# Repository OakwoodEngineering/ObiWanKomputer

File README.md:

# Obi Wan Komputer and Combined Payload Board
## Oakwood Engineering, NyanSat Project

Welcome to the public git repository for NyanSat's OBC and payload board.  We hope that this project will be generally useful for the CubeSat community.  NyanSat is a 2U CubeSat selected by NASA's CubeSat Launch Initiative and made by high school students at [Oakwood School](https://oakwoodway.org).

[NyanSat Obi Wan Komputer and Combined Payload Board](https://github.com/OakwoodEngineering/ObiWanKomputer) by [Oakwood Engineering](https://nyansat.org) is licensed under [Creative Commons Attribution-ShareAlike 4.0 International](https://creativecommons.org/licenses/by-sa/4.0/?ref=chooser-v1)    

It is based on the [PyCubed](https://pycubed.org) flight computer by Max Holliday.

The design was made with [Kicad EDA](https://www.kicad.org/) version 8 and is in the hardware directory.  More details to come.

For now, an overview of the design is in the following poster presented at Cal Poly's [CubeSat Developer Workshop](https://www.cubesatdw.org/) 2025 (click for PDF):

You can also visit our website at [nyansat.org](https://nyansat.org).

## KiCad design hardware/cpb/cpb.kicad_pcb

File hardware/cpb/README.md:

# NyanSat
## Combined Payload Board

The Combined Payload Board (CPB) is a component of the NyanSat project, designed to interface with a variety of payloads, including imaging, material science experiments, the Attitude Determination and Control Subsystem (ADACS), and the acoustic spacecraft mapping subsystem.

### Internal Interfaces
* Mechanical: PC/104 form factor for holes and board outline.
    * SMT components all on bottom side of board; top side for connectors and stacking Raspberry Pi Zero 2W.
* 40 pin spacecraft electrical bus
	* Battery voltage (post-inhibit switches, current sensing, current limiting on OBC).
	* One GPIO: Gating of battery voltage to board except bridge driver
    * One GPIO: Gating of battery voltage to bridge driver
	* I2C
		* I2C-UART Address: `0x90 = 1001 0000`
            * Raspberry Pi: controlled by serial from I2C-UART.
            * Pi power controlled by I2C-UART GPIO
            * 3 external power switches controlled by I2C-UART GPIOs.
        * I2C-SPI converter for driver bridges `0x50 = 0101 000X`
            * MAX22200 bridge chip select, command select, and enable controlled by I2C-SPI converter.
		* Microcontroller Address: TBD
	* Ground/return path for power and all signals
* Mounting holes
	* 0603 pads from holes to board ground exist; can populate with capacitor (AC-couple to stack), resistor, short, or leave open.

### External Interfaces
* 4 versatile analog inputs. provided by microcontroller ADC, 0-3.3V 12 bit 1.1MSPS.  Pads on board allow selections of various modes:
	* Divided voltage or pulled towards chosen voltage
	* Resistive termination or known impedance
	* AC coupling
    * Pin alternate functions allow use for digital inputs or timer outputs
* 2 DC (0-5V) or AC-coupled waveform generation channels produced from microcontroller DAC with ~40mA drive capability
	* Controlled by microcontroller; feedback to ADC allows precise control of voltages.
	* Low pass filter: 2nd order with -3dB bandwidth of 100KHz.
* 8 high-side switches of battery voltage for payloads and magnetorquers
	* 3 controlled by GPIO from I2C-UART peripheral
	* 1 controlled by onboard Raspberry Pi computer
	* 4 controlled by onboard Cortex-M0+ microcontroller
* 8 half-bridges with programmable current limits
* 5 pin connection for external I2C peripheral (e.g. magnetometer)
* On Pi: CSI interface for Raspberry Pi camera

### Anticipated Use
* Attitude Determination and Control Subsystem (ADACS):
	* Switches: 3 magnetorquers, bipolar (6 half-bridges)
* Acoustic Spacecraft Sounding:
	* Switch: Solenoid, driven by pair of half-bridges
	* Possible switch: MEMS microphone power
	* ADC: 2 channels of MEMS microphone.
* Material science / semiconductor characterization experiment  
	* Waveform generation: 2 channels of drive voltages.
	* ADC: 2 channels of measurement.
* Camera
	* Pi/CSI to camera.
	* Possible high powered LED via high side driver.
* Deployables
	* Option open to use high-side switches channels from here for deployment.
	* Consider using this board to energize second deployable resistor for redundancy.

### Stored-Program Computing Components
* Microcontroller; used mostly as a smart ADC/DAC.
	* STM32L072RBT6; 32MHz Cortex-M0+ with single-cycle multiplier, 128k flash, 6k data EEPROM, 20k RAM.
* Raspberry Pi Zero 2W; used mostly as interface for camera.
	* Quad-core Cortex A53 64-bit processor, 512MB SDRAM.
	* Wireless capabilities (disabled in flight) can be used for ground troubleshooting.
	* Use SLC microSD card, e.g. SFSD2048N1BN1WI-E-QF-111-STD from SwissBit.

### Design Philosophy
* Board's power is gated and will be completely de-powered if a pin on spacecraft electrical bus is not driven high.
* Seperate power gate for magnetorquer full-bridge.
* No high-level sequencing of experiments performed by this board; enabled and commanded from main On-Board Computer (OBC).
* I2C is isolated from spacecraft bus if de-powered or peripheral locks up.
* Large portions of functionality work even if non-volatile memory on a device is corrupted.
	* I2C-UART/GPIO chip does not have nonvolatile memory, and directly controls 4 output switches.
    * I2C-SPI and MAX22200 do not have nonvolatile state.
	* Microcontroller starts up held in reset until explicitly enabled by I2C-UART.
	* If microcontroller is corrupted, Raspberry Pi is capable of reprogramming via on-chip debug features.
    * Pi's power supply is separately enabled by I2C-UART.
	* If Pi filesystem is corrupted, small chance of recovery through failsafe pin (indicates to boot from different part of SD card).

### Known Weaknesses & Shortcomings
* No provision to measure power used by this board.
* No real current limiting beyond master current limiting from ADM1176 PMIC on OBC.
	* But: If entire satellite resets due to overcurrent, this board will revert to default state (turned off).
    * 200 mohm resistors and FET Rds do provide a little bit of mitigation of catastrophes.
* Raspberry Pi must be turned on to generate waveforms / run matsci experiment due to board architecture (needs 5V rail).
* Only having 4 ADC is a little limiting.

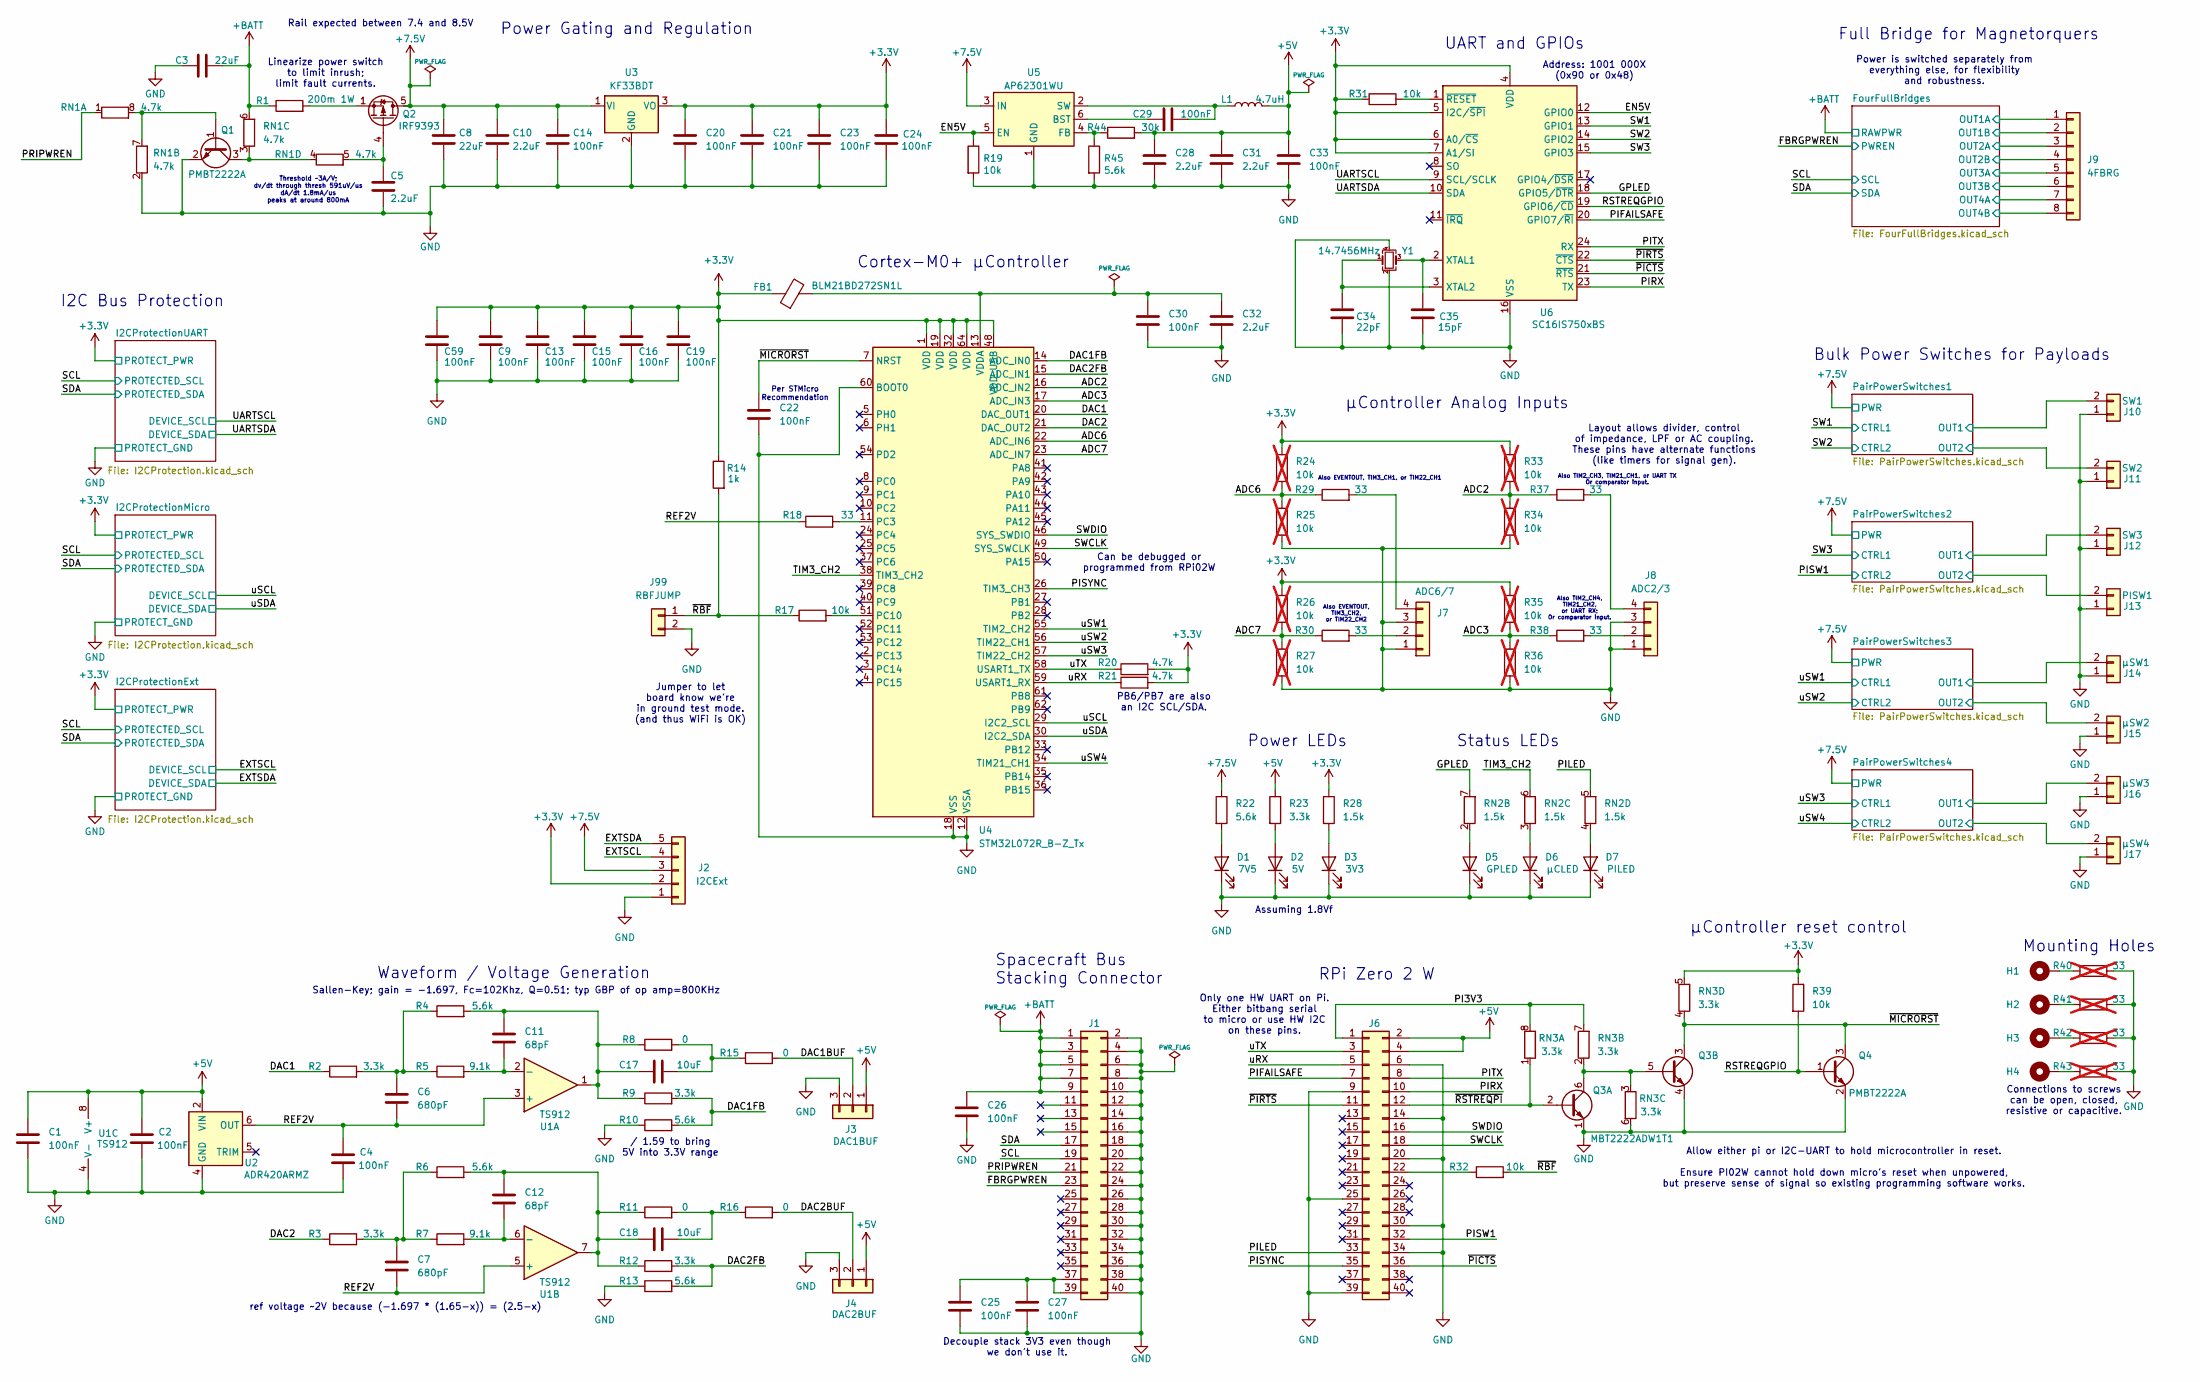
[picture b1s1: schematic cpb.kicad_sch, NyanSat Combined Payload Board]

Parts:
C1, C2, C4, C9, C13, C14, C15, C16, C19, C20, C21, C22, C23, C24, C25, C26, C27, C29, C30, C33, C59: 100nF; C_0603_1608Metric
C3, C8: 22uF; C_0805_2012Metric
C5, C10, C28, C31, C32: 2.2uF; C_0603_1608Metric
C6, C7: 680pF; C_0603_1608Metric
C11, C12: 68pF; C_0603_1608Metric
C17, C18: 10uF; C_0603_1608Metric
C34: 22pF; C_0603_1608Metric
C35: 15pF; C_0603_1608Metric
D1: 7V5; LED_0805_2012Metric; LCSC C84256
D2: 5V; LED_0805_2012Metric; LCSC C84256
D3: 3V3; LED_0805_2012Metric; LCSC C84256
D5: GPLED; LED_0805_2012Metric; LCSC C84256
D6: μCLED; LED_0805_2012Metric; LCSC C84256
D7: PILED; LED_0805_2012Metric; LCSC C84256
FB1: BLM21BD272SN1L; L_0805_2012Metric; LCSC C85839
H1, H2, H3, H4: MountingHole_Pad; MountingHole_3.2mm_M3_DIN965_Pad
J1: Spacecraft Bus Stacking Connector; PinHeader_2x20_P2.54mm_Vertical
J2: I2CExt; JST_PH_B5B-PH-K_1x05_P2.00mm_Vertical
J3: DAC1BUF; JST_PH_B3B-PH-K_1x03_P2.00mm_Vertical
J4: DAC2BUF; JST_PH_B3B-PH-K_1x03_P2.00mm_Vertical
J6: Raspberry Pi Zero 2W; RPI02W
J7: ADC6/7; JST_PH_B4B-PH-K_1x04_P2.00mm_Vertical
J8: ADC2/3; JST_PH_B4B-PH-K_1x04_P2.00mm_Vertical
J9: 4FBRG; JST_PHD_B8B-PHDSS_2x04_P2.00mm_Vertical
J10: SW1; JST_PH_B2B-PH-K_1x02_P2.00mm_Vertical
J11: SW2; JST_PH_B2B-PH-K_1x02_P2.00mm_Vertical
J12: SW3; JST_PH_B2B-PH-K_1x02_P2.00mm_Vertical
J13: PISW1; JST_PH_B2B-PH-K_1x02_P2.00mm_Vertical
J14: μSW1; JST_PH_B2B-PH-K_1x02_P2.00mm_Vertical
J15: μSW2; JST_PH_B2B-PH-K_1x02_P2.00mm_Vertical
J16: μSW3; JST_PH_B2B-PH-K_1x02_P2.00mm_Vertical
J17: μSW4; JST_PH_B2B-PH-K_1x02_P2.00mm_Vertical
J99: RBFJUMP; SolderJumper-2_P1.3mm_Open_TrianglePad1.0x1.5mm
L1: 4.7uH; L_Vishay_IHLP-2020; LCSC C844991
Q1, Q4: PMBT2222A; SOT-23; LCSC C23869
Q2: IRF9393; SOIC-8_3.9x4.9mm_P1.27mm; LCSC C520642
Q3: MBT2222ADW1T1; SOT-363_SC-70-6; LCSC C157366
R1: 200m 1W; R_1206_3216Metric
R2, R3, R9, R12, R23: 3.3k; R_0603_1608Metric
R4, R6, R10, R13, R22, R45: 5.6k; R_0603_1608Metric
R5, R7: 9.1k; R_0603_1608Metric
R8, R11, R15, R16: 0; R_0603_1608Metric
R14: 1k; R_0603_1608Metric
R17, R19, R31, R32, R39: 10k; R_0603_1608Metric
R18, R29, R30, R37, R38: 33; R_0603_1608Metric
R20, R21: 4.7k; R_0603_1608Metric
R24, R25, R26, R27, R33, R34, R35, R36: 10k; R_0603_1608Metric; not fitted
R28: 1.5k; R_0603_1608Metric
R40, R41, R42, R43: 33; R_0603_1608Metric; not fitted
R44: 30k; R_0603_1608Metric
RN1: 4.7k; R_Array_Convex_4x0603
RN2: 1.5k; R_Array_Convex_4x0603
RN3: 3.3k; R_Array_Convex_4x0603
U1: TS912; SOIC-8_3.9x4.9mm_P1.27mm; LCSC C73655
U2: ADR420ARMZ; MSOP-8_3x3mm_P0.65mm; LCSC C208143
U3: KF33BDT; TO-252-2; LCSC C283274
U4: STM32L072R_B-Z_Tx; LQFP-64_10x10mm_P0.5mm; LCSC C915968
U5: AP62301WU; TSOT-23-6
U6: SC16IS750xBS; HVQFN-24-1EP_4x4mm_P0.5mm_EP2.5x2.5mm; LCSC C2651891
Y1: 14.7456MHz; Crystal_SMD_3225-4Pin_3.2x2.5mm

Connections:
+3.3V: C9.1, C13.1, C15.1, C16.1, C19.1, C20.1, C21.1, C23.1, C24.1, C59.1, FB1.1, J2.2, R14.1, R20.2, R21.2, R24.1, R26.1, R28.1, R31.1, R33.1, R35.1, R39.1, RN3.5 (R4.2), U3.3 (VO), U4.1 (VDD), U4.19 (VDD), U4.32 (VDD), U4.48 (VDD_USB), U4.64 (VDD), U6.4 (VDD), U6.5 (I2C/~SPI), U6.6 (A0/~CS), U6.7 (A1/SI); also elsewhere on the board
+5V: C1.1, C2.1, C28.1, C31.1, C33.1, J3.1, J4.1, J6.2, J6.4, L1.2, R23.1, R44.2, U1.8 (V+), U2.2 (VIN)
+7.5V: C8.1, C10.1, C14.1, J2.3, Q2.5 (D), Q2.6 (D), Q2.7 (D), Q2.8 (D), R22.1, U3.1 (VI), U5.3 (IN); also elsewhere on the board
+BATT: C3.2, C26.1, J1.1, J1.3, J1.5, J1.7, J1.9, R1.1, RN1.6 (R3.2); also elsewhere on the board
/ADC2: R33.2, R34.1, R37.1, U4.16 (ADC_IN2)
/ADC3: R35.2, R36.1, R38.1, U4.17 (ADC_IN3)
/ADC6: R24.2, R25.1, R29.1, U4.22 (ADC_IN6)
/ADC7: R26.2, R27.1, R30.1, U4.23 (ADC_IN7)
/DAC1: R2.1, U4.20 (DAC_OUT1)
/DAC1BUF: J3.2, R15.2
/DAC1FB: R9.2, R10.2, U4.14 (ADC_IN0)
/DAC2: R3.1, U4.21 (DAC_OUT2)
/DAC2BUF: J4.2, R16.2
/DAC2FB: R12.2, R13.2, U4.15 (ADC_IN1)
/EN5V: R19.1, U5.5 (EN), U6.12 (GPIO0)
/EXTSCL: J2.4; also elsewhere on the board
/EXTSDA: J2.5; also elsewhere on the board
/FBRGPWREN: J1.23; also elsewhere on the board
/FourFullBridges/OUT1A: J9.1; also elsewhere on the board
/FourFullBridges/OUT1B: J9.2; also elsewhere on the board
/FourFullBridges/OUT2A: J9.3; also elsewhere on the board
/FourFullBridges/OUT2B: J9.4; also elsewhere on the board
/FourFullBridges/OUT3A: J9.5; also elsewhere on the board
/FourFullBridges/OUT3B: J9.6; also elsewhere on the board
/FourFullBridges/OUT4A: J9.7; also elsewhere on the board
/FourFullBridges/OUT4B: J9.8; also elsewhere on the board
/GPLED: RN2.7 (R2.2), U6.18 (GPIO5/~DTR)
/PI3V3: J6.1, RN3.7 (R2.2), RN3.8 (R1.2)
/PIFAILSAFE: J6.7, U6.20 (GPIO7/~RI)
/PILED: J6.33, RN2.5 (R4.2)
/PIRX: J6.10, U6.23 (TX)
/PISW1: J6.32; also elsewhere on the board
/PISYNC: J6.35, U4.26 (TIM3_CH3)
/PITX: J6.8, U6.24 (RX)
/PRIPWREN: J1.21, RN1.1 (R1.1)
/PairPowerSwitches1/OUT1: J10.2; also elsewhere on the board
/PairPowerSwitches1/OUT2: J11.2; also elsewhere on the board
/PairPowerSwitches2/OUT1: J12.2; also elsewhere on the board
/PairPowerSwitches2/OUT2: J13.2; also elsewhere on the board
/PairPowerSwitches3/OUT1: J14.2; also elsewhere on the board
/PairPowerSwitches3/OUT2: J15.2; also elsewhere on the board
/PairPowerSwitches4/OUT1: J16.2; also elsewhere on the board
/PairPowerSwitches4/OUT2: J17.2; also elsewhere on the board
/REF2V: C4.1, C6.2, C7.2, R18.1, U1.3 (+), U1.5 (+), U2.6 (OUT)
/RSTREQGPIO: Q4.1 (B), R39.2, U6.19 (GPIO6/~CD)
/SCL: J1.19; also elsewhere on the board
/SDA: J1.17; also elsewhere on the board
/SW1: U6.13 (GPIO1); also elsewhere on the board
/SW2: U6.14 (GPIO2); also elsewhere on the board
/SW3: U6.15 (GPIO3); also elsewhere on the board
/SWCLK: J6.18, U4.49 (SYS_SWCLK)
/SWDIO: J6.16, U4.46 (SYS_SWDIO)
/TIM3_CH2: RN2.6 (R3.2), U4.38 (TIM3_CH2)
/UARTSCL: U6.9 (SCL/SCLK); also elsewhere on the board
/UARTSDA: U6.10 (SDA); also elsewhere on the board
/uRX: J6.5, R21.1, U4.59 (USART1_RX)
/uSCL: U4.29 (I2C2_SCL); also elsewhere on the board
/uSDA: U4.30 (I2C2_SDA); also elsewhere on the board
/uSW1: U4.55 (TIM2_CH2); also elsewhere on the board
/uSW2: U4.56 (TIM22_CH1); also elsewhere on the board
/uSW3: U4.57 (TIM22_CH2); also elsewhere on the board
/uSW4: U4.34 (TIM21_CH1); also elsewhere on the board
/uTX: J6.3, R20.1, U4.58 (USART1_TX)
/~MICRORST: C22.1, Q3.3 (C2), Q4.3 (C), RN3.4 (R4.1), U4.7 (NRST)
/~PICTS: J6.36, U6.21 (~RTS)
/~PIRTS: J6.11, U6.22 (~CTS)
/~RBF: J99.1, R14.2, R17.1, R32.2
/~RSTREQPI: J6.12, Q3.2 (B1), RN3.1 (R1.1)
GND: C1.2, C2.2, C3.1, C4.2, C5.2, C8.2, C9.2, C10.2, C13.2, C14.2, C15.2, C16.2, C19.2, C20.2, C21.2, C22.2, C23.2, C24.2, C25.2, C26.2, C27.2, C28.2, C30.2, C31.2, C32.2, C33.2, C34.2, C35.2, C59.2, D1.1 (K), D2.1 (K), D3.1 (K), D5.1 (K), D6.1 (K), D7.1 (K), J1.2, J1.4, J1.6, J1.8, J1.10, J1.12, J1.14, J1.16, J1.18, J1.20, J1.22, J1.24, J1.26, J1.28, J1.30, J1.32, J1.34, J1.36, J1.38, J1.40, J2.1, J3.3, J4.3, J6.6, J6.9, J6.14, J6.20, J6.25, J6.30, J6.34, J6.39, J7.1, J7.3, J8.1, J8.3, J10.1, J11.1, J12.1, J13.1, J14.1, J15.1, J16.1, J17.1, J99.2, Q1.2 (E), Q3.1 (E1), Q3.4 (E2), Q4.2 (E), R10.1, R13.1, R19.2, R25.2, R27.2, R34.2, R36.2, R40.2, R41.2, R42.2, R43.2, R45.2, RN1.2 (R2.1), RN3.6 (R3.2), U1.4 (V-), U2.4 (GND), U3.2 (GND), U4.12 (VSSA), U4.18 (VSS), U4.31 (VSS), U4.47 (VSS), U4.60 (BOOT0), U4.63 (VSS), U5.1 (GND), U6.16 (VSS), U6.25 (VSS), Y1.2, Y1.4; also elsewhere on the board
unnamed: C6.1, R2.2, R4.1, R5.1
unnamed: C7.1, R3.2, R6.1, R7.1
unnamed: C11.1, C17.1, R4.2, R8.1, R9.1, U1.1
unnamed: C12.1, C18.1, R6.2, R11.1, R12.1, U1.7
unnamed: C17.2, R8.2, R15.1
unnamed: C18.2, R11.2, R16.1
unnamed: D1.2 (A), R22.2
unnamed: D2.2 (A), R23.2
unnamed: D3.2 (A), R28.2
unnamed: D5.2 (A), RN2.2 (R2.1)
unnamed: D6.2 (A), RN2.3 (R3.1)
unnamed: D7.2 (A), RN2.4 (R4.1)
unnamed: H1.1, R40.1
unnamed: H2.1, R41.1
unnamed: H3.1, R42.1
unnamed: H4.1, R43.1
unnamed: C25.1, C27.1, J1.37, J1.39
unnamed: J6.22, R32.1
unnamed: J7.2, R30.2
unnamed: J7.4, R29.2
unnamed: J8.2, R38.2
unnamed: J8.4, R37.2
unnamed: Q1.1 (B), RN1.7 (R2.2), RN1.8 (R1.2)
unnamed: Q1.3 (C), RN1.3 (R3.1), RN1.4 (R4.1)
unnamed: C5.1, Q2.4 (G), RN1.5 (R4.2)
unnamed: Q2.1 (S), Q2.2 (S), Q2.3 (S), R1.2
unnamed: Q3.5 (B2), Q3.6 (C1), RN3.2 (R2.1), RN3.3 (R3.1)
unnamed: C11.2, R5.2, U1.2 (-)
unnamed: C12.2, R7.2, U1.6 (-)
unnamed: R18.2, U4.11 (PC3)
unnamed: R17.2, U4.51 (PC10)
unnamed: C30.1, C32.1, FB1.2, U4.13 (VDDA)
unnamed: C29.1, U5.6 (BST)
unnamed: R44.1, R45.1, U5.4 (FB)
unnamed: C29.2, L1.1, U5.2 (SW)
unnamed: C35.1, U6.2 (XTAL1), Y1.3
unnamed: C34.1, U6.3 (XTAL2), Y1.1
unnamed: R31.2, U6.1 (~RESET)

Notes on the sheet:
Also TIM2_CH3, TIM21_CH1, or UART TX Or comparator input.
Bulk Power Switches for Payloads
Connections to screws can be open, closed, resistive or capacitive.
μController Analog Inputs
Power LEDs
Can be debugged or programmed from RPi02W
Allow either pi or I2C-UART to hold microcontroller in reset. Ensure PI02W cannot hold down micro's reset when unpowered, but preserve sense of signal so existing programming software works.
Threshold ~3A/V; dv/dt through thresh 591uV/us dA/dt 1.8mA/us peaks at around 800mA
Only one HW UART on Pi. Either bitbang serial to micro or use HW I2C on these pins.
Decouple stack 3V3 even though we don't use it.
Power Gating and Regulation
ref voltage ~2V because (-1.697 * (1.65-x)) = (2.5-x)
PB6/PB7 are also an I2C SCL/SDA.
Also TIM2_CH4, TIM21_CH2, or UART RX; Or comparator input.
Rail expected between 7.4 and 8.5V
Power is switched separately from everything else, for flexibility and robustness.
Mounting Holes
μController reset control
Sallen-Key; gain = -1.697, Fc=102Khz, Q=0.51; typ GBP of op amp=800KHz
RPi Zero 2 W
Assuming 1.8Vf
Also EVENTOUT, TIM3_CH2, or TIM22_CH2
Layout allows divider, control of impedance, LPF or AC coupling. These pins have alternate functions (like timers for signal gen).
Address: 1001 000X (0x90 or 0x48)
Status LEDs
UART and GPIOs
Linearize power switch to limit inrush; limit fault currents.
Jumper to let board know we're in ground test mode. (and thus WiFi is OK)
Per STMicro Recommendation
/ 1.59 to bring 5V into 3.3V range
Spacecraft Bus Stacking Connector
Also EVENTOUT, TIM3_CH1, or TIM22_CH1
Waveform / Voltage Generation
Cortex-M0+ μController
Full Bridge for Magnetorquers
I2C Bus Protection

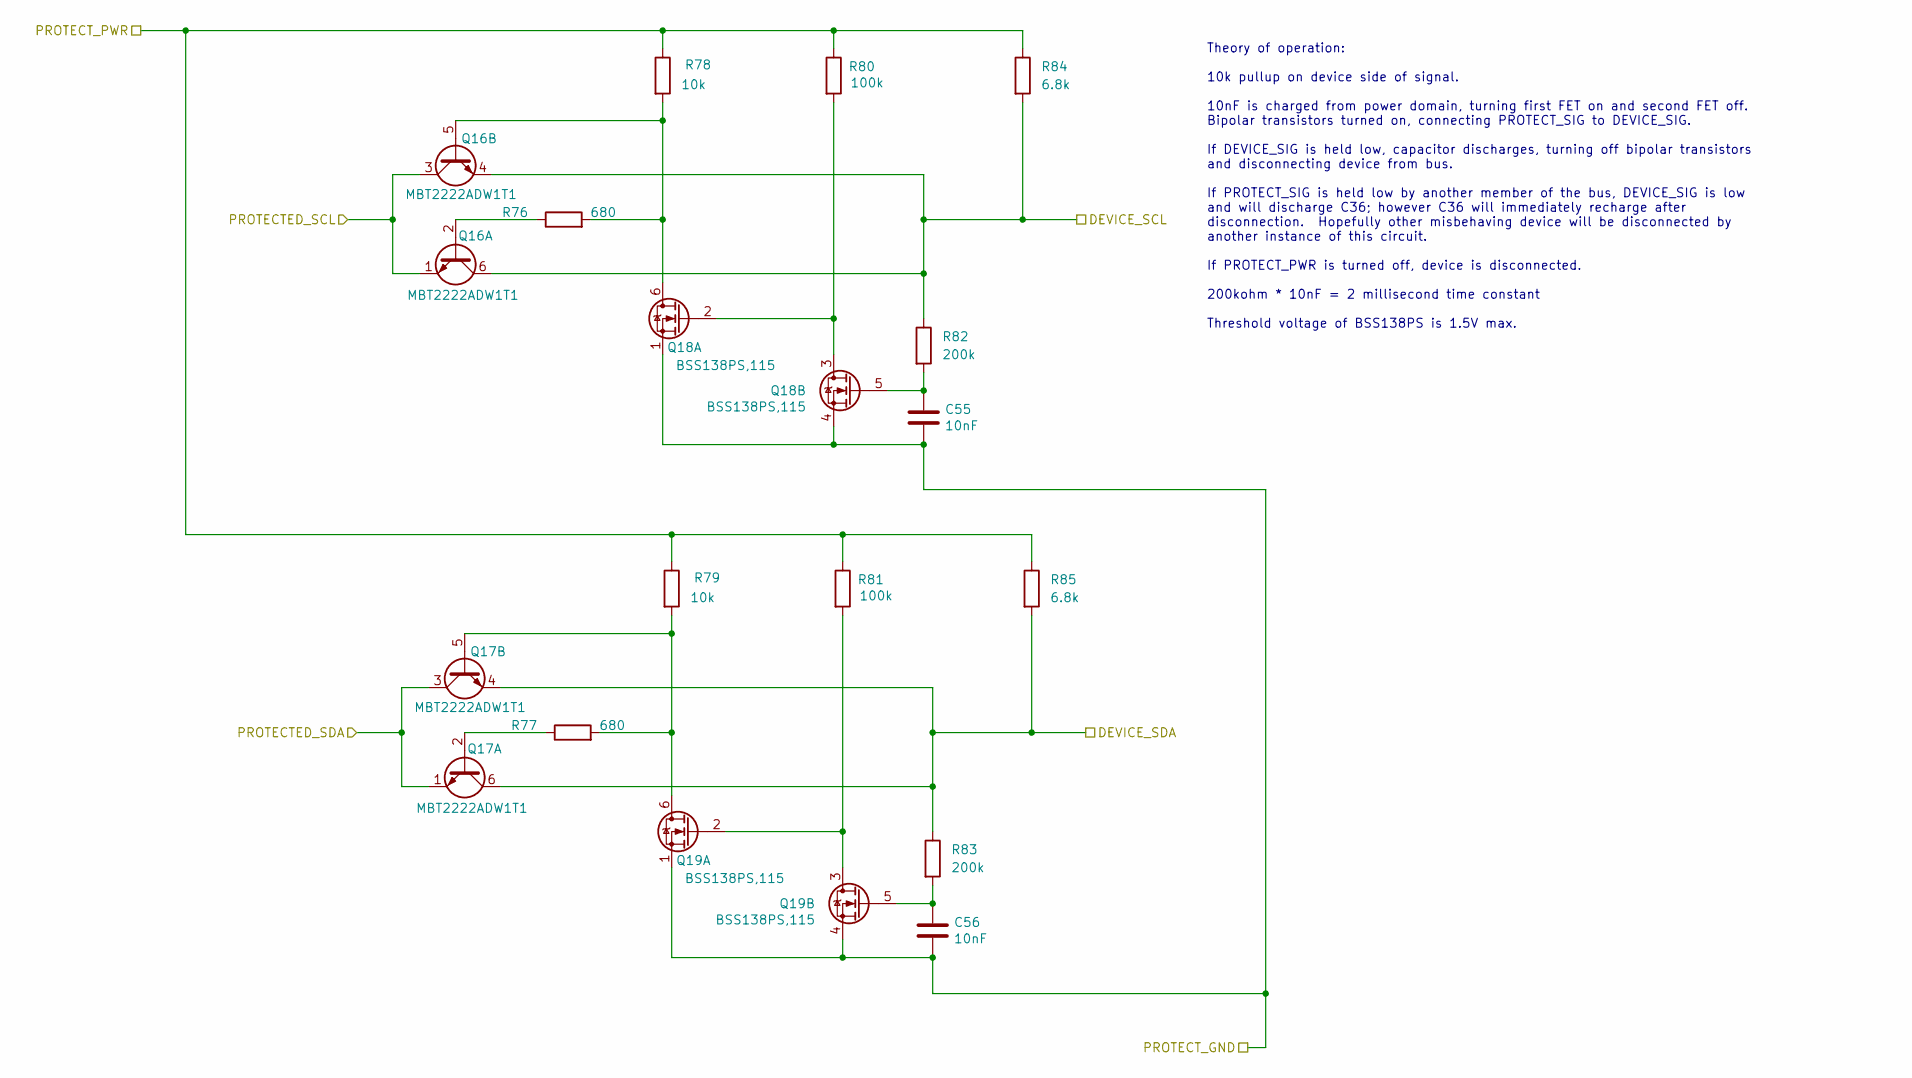
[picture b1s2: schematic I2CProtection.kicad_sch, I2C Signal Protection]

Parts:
C55, C56: 10nF; C_0603_1608Metric
Q16, Q17: MBT2222ADW1T1; SOT-363_SC-70-6; LCSC C157366
Q18, Q19: BSS138PS,115; SOT-363_SC-70-6; LCSC C193381
R76, R77: 680; R_0603_1608Metric
R78, R79: 10k; R_0603_1608Metric
R80, R81: 100k; R_0603_1608Metric
R82, R83: 200k; R_0603_1608Metric
R84, R85: 6.8k; R_0603_1608Metric

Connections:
+3.3V: R78.1, R79.1, R80.1, R81.1, R84.1, R85.1; also elsewhere on the board
/SCL: Q16.1 (E1), Q16.3 (C2); also elsewhere on the board
/SDA: Q17.1 (E1), Q17.3 (C2); also elsewhere on the board
/uSCL: Q16.4 (E2), Q16.6 (C1), R82.1, R84.2; also elsewhere on the board
/uSDA: Q17.4 (E2), Q17.6 (C1), R83.1, R85.2; also elsewhere on the board
GND: C55.2, C56.2, Q18.1 (S2), Q18.4 (S1), Q19.1 (S2), Q19.4 (S1); also elsewhere on the board
unnamed: Q16.2 (B1), R76.1
unnamed: Q16.5 (B2), Q18.6 (D1), R76.2, R78.2
unnamed: Q17.2 (B1), R77.1
unnamed: Q17.5 (B2), Q19.6 (D1), R77.2, R79.2
unnamed: Q18.2 (G2), Q18.3 (D2), R80.2
unnamed: C55.1, Q18.5 (G1), R82.2
unnamed: Q19.2 (G2), Q19.3 (D2), R81.2
unnamed: C56.1, Q19.5 (G1), R83.2

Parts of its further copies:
C51, C52, C53, C54, C57, C58: 10nF; C_0603_1608Metric
Q8, Q9, Q12, Q13, Q20, Q21: MBT2222ADW1T1; SOT-363_SC-70-6; LCSC C157366
Q10, Q11, Q14, Q15, Q22, Q23: BSS138PS,115; SOT-363_SC-70-6; LCSC C193381
R56, R57, R66, R67, R86, R87: 680; R_0603_1608Metric
R58, R59, R68, R69, R88, R89: 10k; R_0603_1608Metric
R60, R61, R70, R71, R90, R91: 100k; R_0603_1608Metric
R62, R63, R72, R73, R92, R93: 200k; R_0603_1608Metric
R64, R65, R74, R75, R94, R95: 6.8k; R_0603_1608Metric

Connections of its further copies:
+3.3V: R68.1, R69.1, R70.1, R71.1, R74.1, R75.1, R88.1, R89.1, R90.1, R91.1, R94.1, R95.1; also elsewhere on the board
/EXTSCL: Q20.4 (E2), Q20.6 (C1), R92.1, R94.2; also elsewhere on the board
/EXTSDA: Q21.4 (E2), Q21.6 (C1), R93.1, R95.2; also elsewhere on the board
/FourFullBridges/FBRDG3V3: R58.1, R59.1, R60.1, R61.1, R64.1, R65.1; also elsewhere on the board
/FourFullBridges/PCVTSCL: Q8.4 (E2), Q8.6 (C1), R62.1, R64.2; also elsewhere on the board
/FourFullBridges/PCVTSDA: Q9.4 (E2), Q9.6 (C1), R63.1, R65.2; also elsewhere on the board
/SCL: Q8.1 (E1), Q8.3 (C2), Q12.1 (E1), Q12.3 (C2), Q20.1 (E1), Q20.3 (C2); also elsewhere on the board
/SDA: Q9.1 (E1), Q9.3 (C2), Q13.1 (E1), Q13.3 (C2), Q21.1 (E1), Q21.3 (C2); also elsewhere on the board
/UARTSCL: Q12.4 (E2), Q12.6 (C1), R72.1, R74.2; also elsewhere on the board
/UARTSDA: Q13.4 (E2), Q13.6 (C1), R73.1, R75.2; also elsewhere on the board
GND: C51.2, C52.2, C53.2, C54.2, C57.2, C58.2, Q10.1 (S2), Q10.4 (S1), Q11.1 (S2), Q11.4 (S1), Q14.1 (S2), Q14.4 (S1), Q15.1 (S2), Q15.4 (S1), Q22.1 (S2), Q22.4 (S1), Q23.1 (S2), Q23.4 (S1); also elsewhere on the board
unnamed: Q8.2 (B1), R56.1
unnamed: Q9.2 (B1), R57.1
unnamed: Q8.5 (B2), Q10.6 (D1), R56.2, R58.2
unnamed: Q10.2 (G2), Q10.3 (D2), R60.2
unnamed: C51.1, Q10.5 (G1), R62.2
unnamed: Q9.5 (B2), Q11.6 (D1), R57.2, R59.2
unnamed: Q11.2 (G2), Q11.3 (D2), R61.2
unnamed: C52.1, Q11.5 (G1), R63.2
unnamed: Q12.2 (B1), R66.1
unnamed: Q12.5 (B2), Q14.6 (D1), R66.2, R68.2
unnamed: Q13.2 (B1), R67.1
unnamed: Q13.5 (B2), Q15.6 (D1), R67.2, R69.2
unnamed: Q14.2 (G2), Q14.3 (D2), R70.2
unnamed: C53.1, Q14.5 (G1), R72.2
unnamed: Q15.2 (G2), Q15.3 (D2), R71.2
unnamed: C54.1, Q15.5 (G1), R73.2
unnamed: Q20.2 (B1), R86.1
unnamed: Q20.5 (B2), Q22.6 (D1), R86.2, R88.2
unnamed: Q21.2 (B1), R87.1
unnamed: Q21.5 (B2), Q23.6 (D1), R87.2, R89.2
unnamed: Q22.2 (G2), Q22.3 (D2), R90.2
unnamed: C57.1, Q22.5 (G1), R92.2
unnamed: Q23.2 (G2), Q23.3 (D2), R91.2
unnamed: C58.1, Q23.5 (G1), R93.2

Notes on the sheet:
Theory of operation: 10k pullup on device side of signal. 10nF is charged from power domain, turning first FET on and second FET off. Bipolar transistors turned on, connecting PROTECT_SIG to DEVICE_SIG. If DEVICE_SIG is held low, capacitor discharges, turning off bipolar transistors and disconnecti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

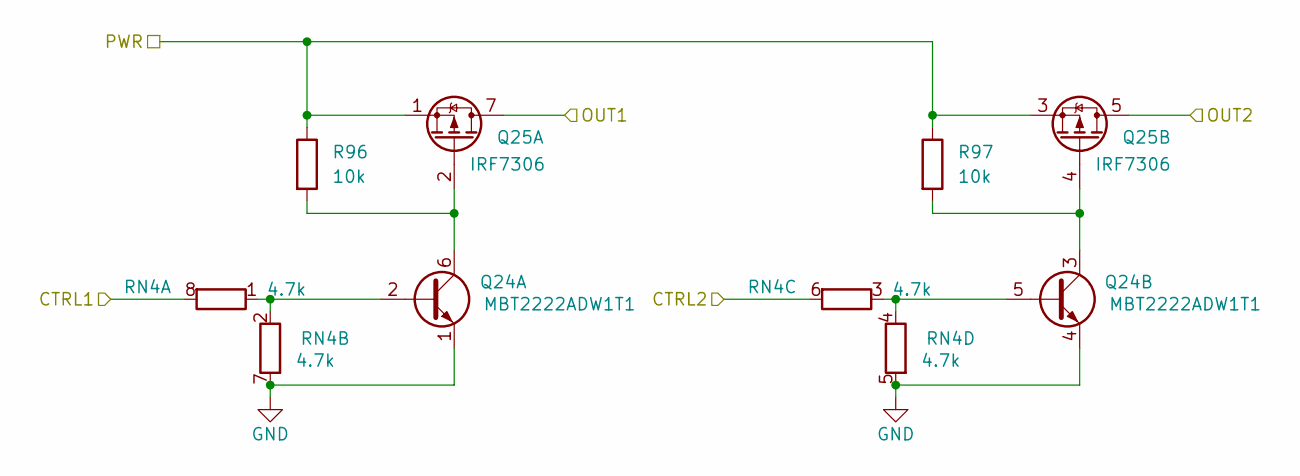
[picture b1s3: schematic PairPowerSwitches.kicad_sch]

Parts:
Q24: MBT2222ADW1T1; SOT-363_SC-70-6; LCSC C157366
Q25: IRF7306; SOIC-8_3.9x4.9mm_P1.27mm; LCSC C537809
R96, R97: 10k; R_0603_1608Metric
RN4: 4.7k; R_Array_Convex_4x0603

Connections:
+7.5V: Q25.1 (S1), Q25.3 (S2), R96.1, R97.1; also elsewhere on the board
/PairPowerSwitches1/OUT1: Q25.7 (D1), Q25.8 (D1); also elsewhere on the board
/PairPowerSwitches1/OUT2: Q25.5 (D2), Q25.6 (D2); also elsewhere on the board
/SW1: RN4.8 (R1.2); also elsewhere on the board
/SW2: RN4.6 (R3.2); also elsewhere on the board
GND: Q24.1 (E1), Q24.4 (E2), RN4.5 (R4.2), RN4.7 (R2.2); also elsewhere on the board
unnamed: Q24.2 (B1), RN4.1 (R1.1), RN4.2 (R2.1)
unnamed: Q24.6 (C1), Q25.2 (G1), R96.2
unnamed: Q24.5 (B2), RN4.3 (R3.1), RN4.4 (R4.1)
unnamed: Q24.3 (C2), Q25.4 (G2), R97.2

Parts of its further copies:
Q26, Q28, Q30: MBT2222ADW1T1; SOT-363_SC-70-6; LCSC C157366
Q27, Q29, Q31: IRF7306; SOIC-8_3.9x4.9mm_P1.27mm; LCSC C537809
R98, R99, R100, R101, R102, R103: 10k; R_0603_1608Metric
RN5, RN6, RN7: 4.7k; R_Array_Convex_4x0603

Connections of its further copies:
+7.5V: Q27.1 (S1), Q27.3 (S2), Q29.1 (S1), Q29.3 (S2), Q31.1 (S1), Q31.3 (S2), R98.1, R99.1, R100.1, R101.1, R102.1, R103.1; also elsewhere on the board
/PISW1: RN5.6 (R3.2); also elsewhere on the board
/PairPowerSwitches2/OUT1: Q27.7 (D1), Q27.8 (D1); also elsewhere on the board
/PairPowerSwitches2/OUT2: Q27.5 (D2), Q27.6 (D2); also elsewhere on the board
/PairPowerSwitches3/OUT1: Q29.7 (D1), Q29.8 (D1); also elsewhere on the board
/PairPowerSwitches3/OUT2: Q29.5 (D2), Q29.6 (D2); also elsewhere on the board
/PairPowerSwitches4/OUT1: Q31.7 (D1), Q31.8 (D1); also elsewhere on the board
/PairPowerSwitches4/OUT2: Q31.5 (D2), Q31.6 (D2); also elsewhere on the board
/SW3: RN5.8 (R1.2); also elsewhere on the board
/uSW1: RN6.8 (R1.2); also elsewhere on the board
/uSW2: RN6.6 (R3.2); also elsewhere on the board
/uSW3: RN7.8 (R1.2); also elsewhere on the board
/uSW4: RN7.6 (R3.2); also elsewhere on the board
GND: Q26.1 (E1), Q26.4 (E2), Q28.1 (E1), Q28.4 (E2), Q30.1 (E1), Q30.4 (E2), RN5.5 (R4.2), RN5.7 (R2.2), RN6.5 (R4.2), RN6.7 (R2.2), RN7.5 (R4.2), RN7.7 (R2.2); also elsewhere on the board
unnamed: Q26.2 (B1), RN5.1 (R1.1), RN5.2 (R2.1)
unnamed: Q26.6 (C1), Q27.2 (G1), R98.2
unnamed: Q26.5 (B2), RN5.3 (R3.1), RN5.4 (R4.1)
unnamed: Q26.3 (C2), Q27.4 (G2), R99.2
unnamed: Q28.2 (B1), RN6.1 (R1.1), RN6.2 (R2.1)
unnamed: Q28.6 (C1), Q29.2 (G1), R100.2
unnamed: Q28.5 (B2), RN6.3 (R3.1), RN6.4 (R4.1)
unnamed: Q28.3 (C2), Q29.4 (G2), R101.2
unnamed: Q30.2 (B1), RN7.1 (R1.1), RN7.2 (R2.1)
unnamed: Q30.6 (C1), Q31.2 (G1), R102.2
unnamed: Q30.5 (B2), RN7.3 (R3.1), RN7.4 (R4.1)
unnamed: Q30.3 (C2), Q31.4 (G2), R103.2

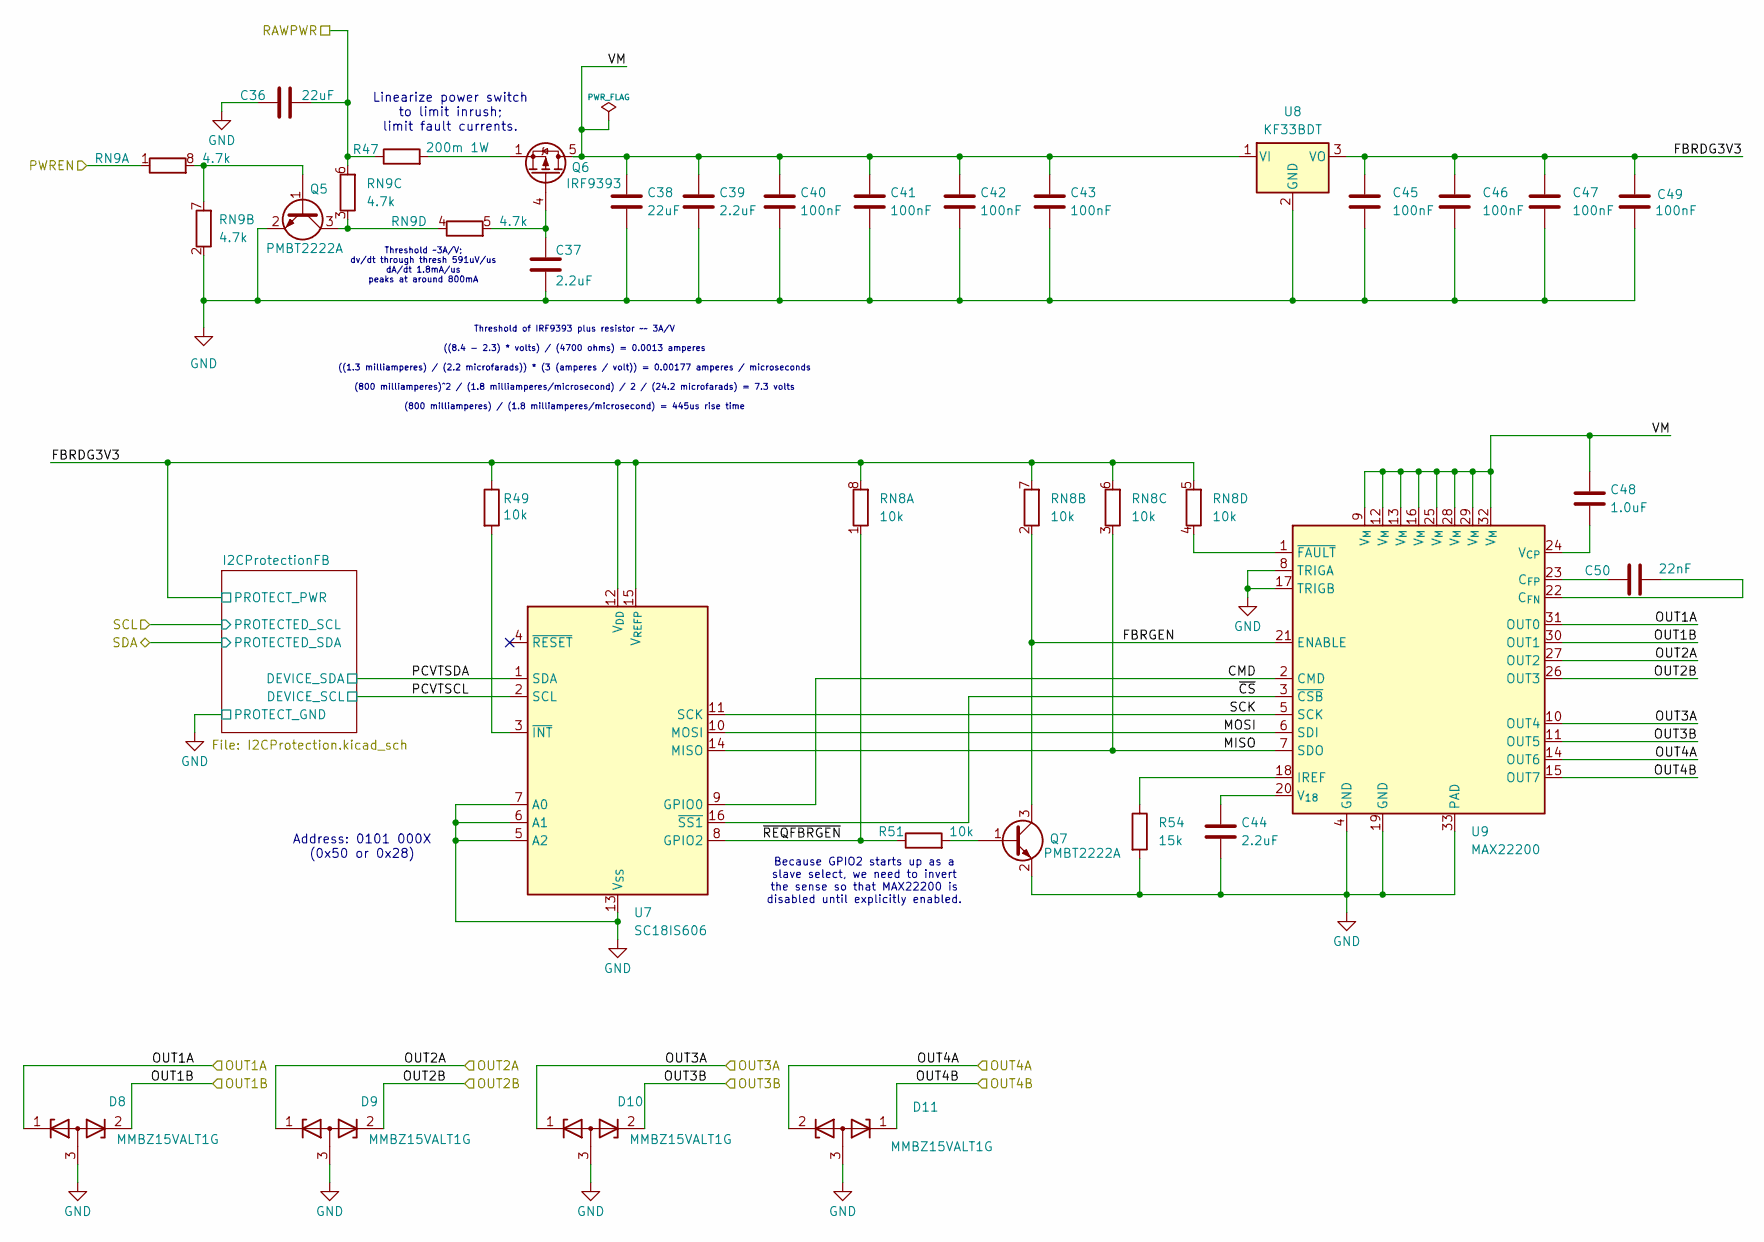
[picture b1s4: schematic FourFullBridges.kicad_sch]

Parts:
C36, C38: 22uF; C_0805_2012Metric
C37, C39, C44: 2.2uF; C_0603_1608Metric
C40, C41, C42, C43, C45, C46, C47, C49: 100nF; C_0603_1608Metric
C48: 1.0uF; C_0603_1608Metric
C50: 22nF; C_0603_1608Metric
D8, D9, D10, D11: MMBZ15VALT1G; SOT-23
Q5, Q7: PMBT2222A; SOT-23; LCSC C23869
Q6: IRF9393; SOIC-8_3.9x4.9mm_P1.27mm; LCSC C520642
R47: 200m 1W; R_1206_3216Metric
R49, R51: 10k; R_0603_1608Metric
R54: 15k; R_0603_1608Metric
RN8: 10k; R_Array_Convex_4x0603
RN9: 4.7k; R_Array_Convex_4x0603
U7: SC18IS606; TSSOP-16_4.4x5mm_P0.65mm
U8: KF33BDT; TO-252-2; LCSC C283274
U9: MAX22200; QFN-32-1EP_5x5mm_P0.5mm_EP3.1x3.1mm_ThermalVias

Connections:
+BATT: C36.2, R47.1, RN9.6 (R3.2); also elsewhere on the board
/FBRGPWREN: RN9.1 (R1.1); also elsewhere on the board
/FourFullBridges/CMD: U7.9 (GPIO0), U9.2 (CMD)
/FourFullBridges/FBRDG3V3: C45.1, C46.1, C47.1, C49.1, R49.1, RN8.5 (R4.2), RN8.6 (R3.2), RN8.7 (R2.2), RN8.8 (R1.2), U7.12 (V_{DD}), U7.15 (V_{REFP}), U8.3 (VO); also elsewhere on the board
/FourFullBridges/FBRGEN: Q7.3 (C), RN8.2 (R2.1), U9.21 (ENABLE)
/FourFullBridges/MISO: RN8.3 (R3.1), U7.14 (MISO), U9.7 (SDO)
/FourFullBridges/MOSI: U7.10 (MOSI), U9.6 (SDI)
/FourFullBridges/OUT1A: D8.1 (K), U9.31 (OUT0); also elsewhere on the board
/FourFullBridges/OUT1B: D8.2 (K), U9.30 (OUT1); also elsewhere on the board
/FourFullBridges/OUT2A: D9.1 (K), U9.27 (OUT2); also elsewhere on the board
/FourFullBridges/OUT2B: D9.2 (K), U9.26 (OUT3); also elsewhere on the board
/FourFullBridges/OUT3A: D10.1 (K), U9.10 (OUT4); also elsewhere on the board
/FourFullBridges/OUT3B: D10.2 (K), U9.11 (OUT5); also elsewhere on the board
/FourFullBridges/OUT4A: D11.2 (K), U9.14 (OUT6); also elsewhere on the board
/FourFullBridges/OUT4B: D11.1 (K), U9.15 (OUT7); also elsewhere on the board
/FourFullBridges/PCVTSCL: U7.2 (SCL); also elsewhere on the board
/FourFullBridges/PCVTSDA: U7.1 (SDA); also elsewhere on the board
/FourFullBridges/SCK: U7.11 (SCK), U9.5 (SCK)
/FourFullBridges/VM: C38.1, C39.1, C40.1, C41.1, C42.1, C43.1, C48.1, Q6.5 (D), Q6.6 (D), Q6.7 (D), Q6.8 (D), U8.1 (VI), U9.9 (V_{M}), U9.12 (V_{M}), U9.13 (V_{M}), U9.16 (V_{M}), U9.25 (V_{M}), U9.28 (V_{M}), U9.29 (V_{M}), U9.32 (V_{M})
/FourFullBridges/~CS: U7.16 (~SS1), U9.3 (~CSB)
/FourFullBridges/~REQFBRGEN: R51.1, RN8.1 (R1.1), U7.8 (GPIO2)
GND: C36.1, C37.2, C38.2, C39.2, C40.2, C41.2, C42.2, C43.2, C44.2, C45.2, C46.2, C47.2, C49.2, D8.3 (A), D9.3 (A), D10.3 (A), D11.3 (A), Q5.2 (E), Q7.2 (E), R54.2, RN9.2 (R2.1), U7.5 (A2), U7.6 (A1), U7.7 (A0), U7.13 (V_{SS}), U8.2 (GND), U9.4 (GND), U9.8 (TRIGA), U9.17 (TRIGB), U9.19 (GND), U9.33 (PAD); also elsewhere on the board
unnamed: Q5.1 (B), RN9.7 (R2.2), RN9.8 (R1.2)
unnamed: Q5.3 (C), RN9.3 (R3.1), RN9.4 (R4.1)
unnamed: C37.1, Q6.4 (G), RN9.5 (R4.2)
unnamed: Q6.1 (S), Q6.2 (S), Q6.3 (S), R47.2
unnamed: Q7.1 (B), R51.2
unnamed: RN8.4 (R4.1), U9.1 (~FAULT)
unnamed: R49.2, U7.3 (~INT)
unnamed: C50.2, U9.22 (C_{FN})
unnamed: C50.1, U9.23 (C_{FP})
unnamed: R54.1, U9.18 (IREF)
unnamed: C44.1, U9.20 (V_{18})
unnamed: C48.2, U9.24 (V_{CP})

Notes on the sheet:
Threshold of IRF9393 plus resistor ~~ 3A/V ((8.4 - 2.3) * volts) / (4700 ohms) = 0.0013 amperes ((1.3 milliamperes) / (2.2 microfarads)) * (3 (amperes / volt)) = 0.00177 amperes / microseconds (800 milliamperes)^2 / (1.8 milliamperes/microsecond) / 2 / (24.2 microfarads) = 7.3 volts (800 milliamper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
Linearize power switch to limit inrush; limit fault currents.
Threshold ~3A/V; dv/dt through thresh 591uV/us dA/dt 1.8mA/us peaks at around 800mA
Because GPIO2 starts up as a slave select, we need to invert the sense so that MAX22200 is disabled until explicitly enabled.
Address: 0101 000X (0x50 or 0x28)
